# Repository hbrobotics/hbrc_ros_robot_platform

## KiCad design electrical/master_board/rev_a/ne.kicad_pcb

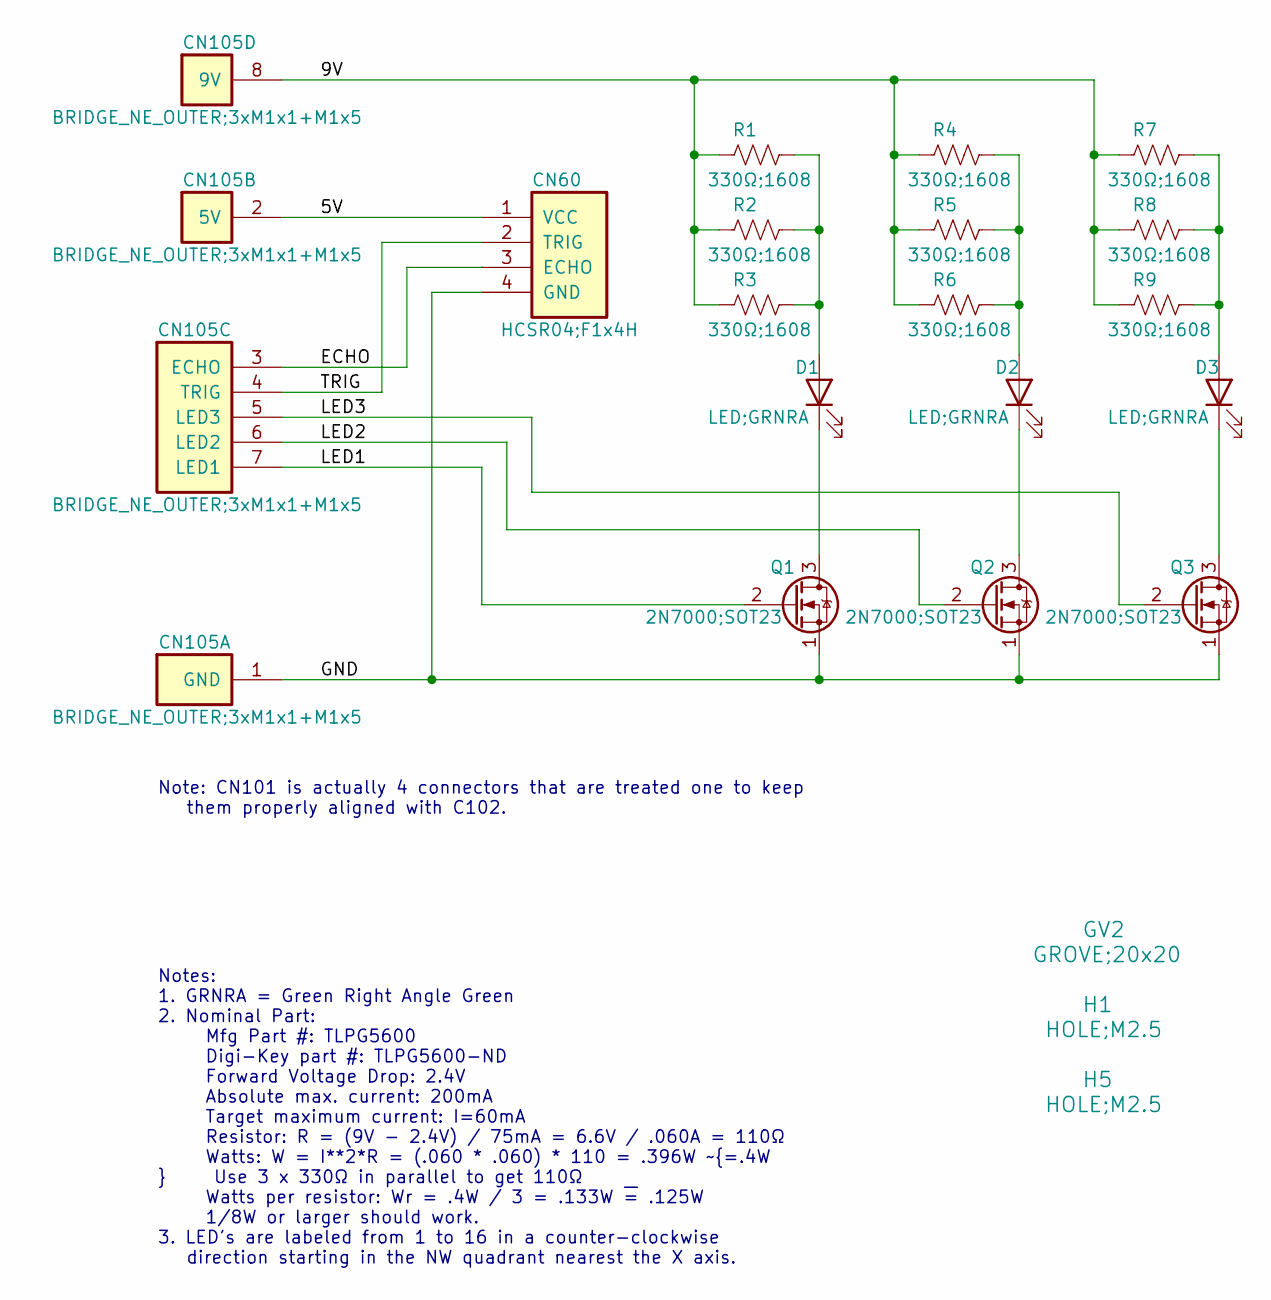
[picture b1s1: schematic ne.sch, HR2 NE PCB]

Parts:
CN60: HCSR04;F1x4H; HCSR04_F1x4H
CN105: BRIDGE_NE_OUTER;3xM1x1+M1x5; BRIDGE_NE_OUTER_3xM1x1+M1x5
D1, D2, D3: LED;GRNRA; LED_GRNRA
GV2: GROVE;20x20; GROVE20x20
H1, H5: HOLE;M2.5; MountingHole_2.7mm_M2.5
Q1, Q2, Q3: 2N7000;SOT23; SOT-23
R1, R2, R3, R4, R5, R6, R7, R8, R9: 330Ω;1608; R_0603_1608Metric

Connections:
/5V: CN60.1 (VCC), CN105.2 (5V)
/9V: CN105.8 (9V), R1.2, R2.2, R3.2, R4.2, R5.2, R6.2, R7.2, R8.2, R9.2
/ECHO: CN60.3 (ECHO), CN105.3 (ECHO)
/GND: CN60.4 (GND), CN105.1 (GND), Q1.1 (S), Q2.1 (S), Q3.1 (S)
/LED1: CN105.7 (LED1), Q1.2 (G)
/LED2: CN105.6 (LED2), Q2.2 (G)
/LED3: CN105.5 (LED3), Q3.2 (G)
/TRIG: CN60.2 (TRIG), CN105.4 (TRIG)
unnamed: D1.1 (K), Q1.3 (D)
unnamed: D1.2 (A), R1.1, R2.1, R3.1
unnamed: D2.1 (K), Q2.3 (D)
unnamed: D2.2 (A), R4.1, R5.1, R6.1
unnamed: D3.1 (K), Q3.3 (D)
unnamed: D3.2 (A), R7.1, R8.1, R9.1

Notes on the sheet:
Notes: 1. GRNRA = Green Right Angle Green 2. Nominal Part: Mfg Part #: TLPG5600 Digi-Key part #: TLPG5600-ND Forward Voltage Drop: 2.4V Absolute max. current: 200mA Target maximum current: I=60mA Resistor: R = (9V - 2.4V) / 75mA = 6.6V / .060A = 110Ω Watts: W = I**2*R = (.060 * .060) * 110 = .396W 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
Note: CN101 is actually 4 connectors that are treated one to keep them properly aligned with C102.

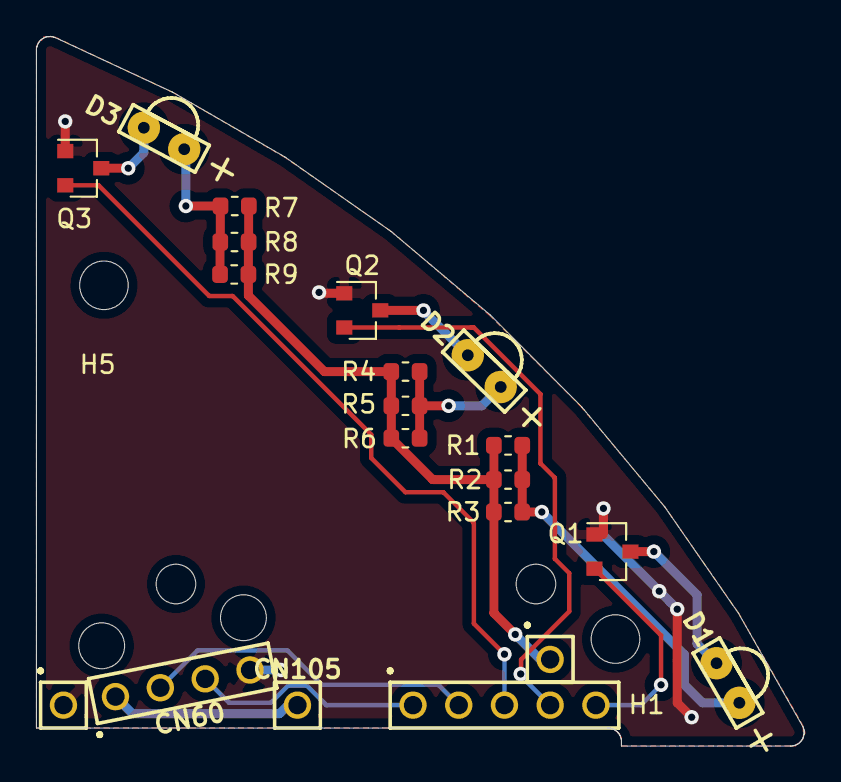
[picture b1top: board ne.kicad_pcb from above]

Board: 2 copper layers, 42.7 x 39.4 mm, 20 parts (1 on the bottom side), 14 nets.

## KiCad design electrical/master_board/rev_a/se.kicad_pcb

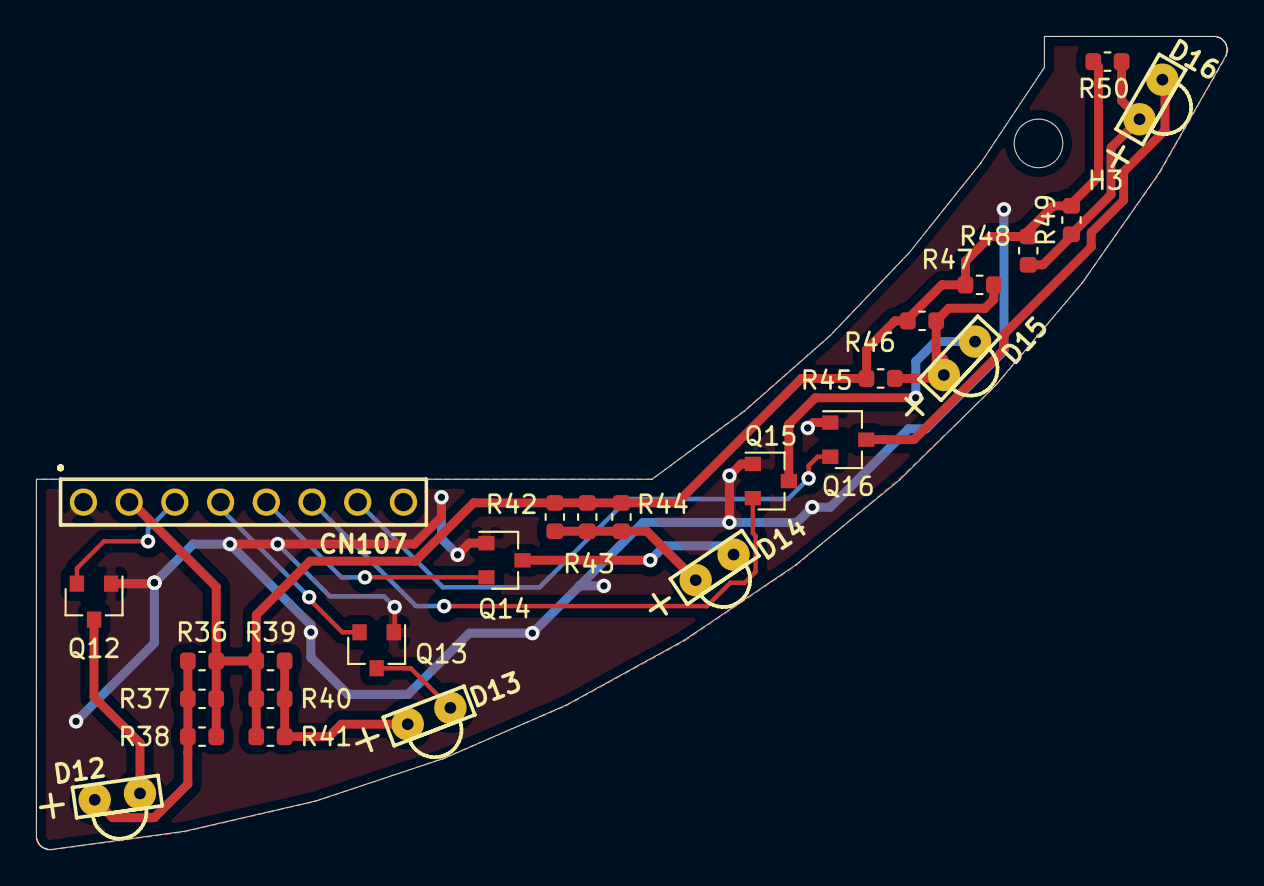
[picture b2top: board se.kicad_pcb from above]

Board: 2 copper layers, 66.2 x 45.2 mm, 27 parts (0 on the bottom side), 17 nets.

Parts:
CN107: BRIDGE_SE_OUTER;M1x8; BRIDGE_SE_OUTER_M1x8
D12, D13, D14, D15, D16: LED;GRNRA; LED_GRNRA
H3: HOLE;M2.5; MountingHole_2.7mm_M2.5
Q12, Q13, Q14, Q15, Q16: 2N7000;SOT23; SOT-23
R36, R37, R38, R39, R40, R41, R42, R43, R44, R45, R46, R47, R48, R49, R50: 330Ω;1608; R_0603_1608Metric

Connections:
/9V: CN107.2, R36.2, R37.2, R38.2, R39.2, R40.2, R41.2, R42.2, R43.2, R44.2, R45.2, R46.2, R47.2, R48.2, R49.2, R50.2
/GND: CN107.1, Q12.1, Q13.1, Q14.1, Q15.1, Q16.1
/LED12: CN107.3, Q12.2
/LED13: CN107.4, Q13.2
/LED14: CN107.5, Q14.2
/LED15: CN107.6, Q15.2
/LED16: CN107.7, Q16.2
unnamed: D12.1, Q12.3
unnamed: D12.2, R36.1, R37.1, R38.1
unnamed: D13.1, Q13.3
unnamed: D13.2, R39.1, R40.1, R41.1
unnamed: D14.1, Q14.3
unnamed: D14.2, R42.1, R43.1, R44.1
unnamed: D15.1, Q15.3
unnamed: D15.2, R45.1, R46.1, R47.1
unnamed: D16.1, Q16.3
unnamed: D16.2, R48.1, R49.1, R50.1

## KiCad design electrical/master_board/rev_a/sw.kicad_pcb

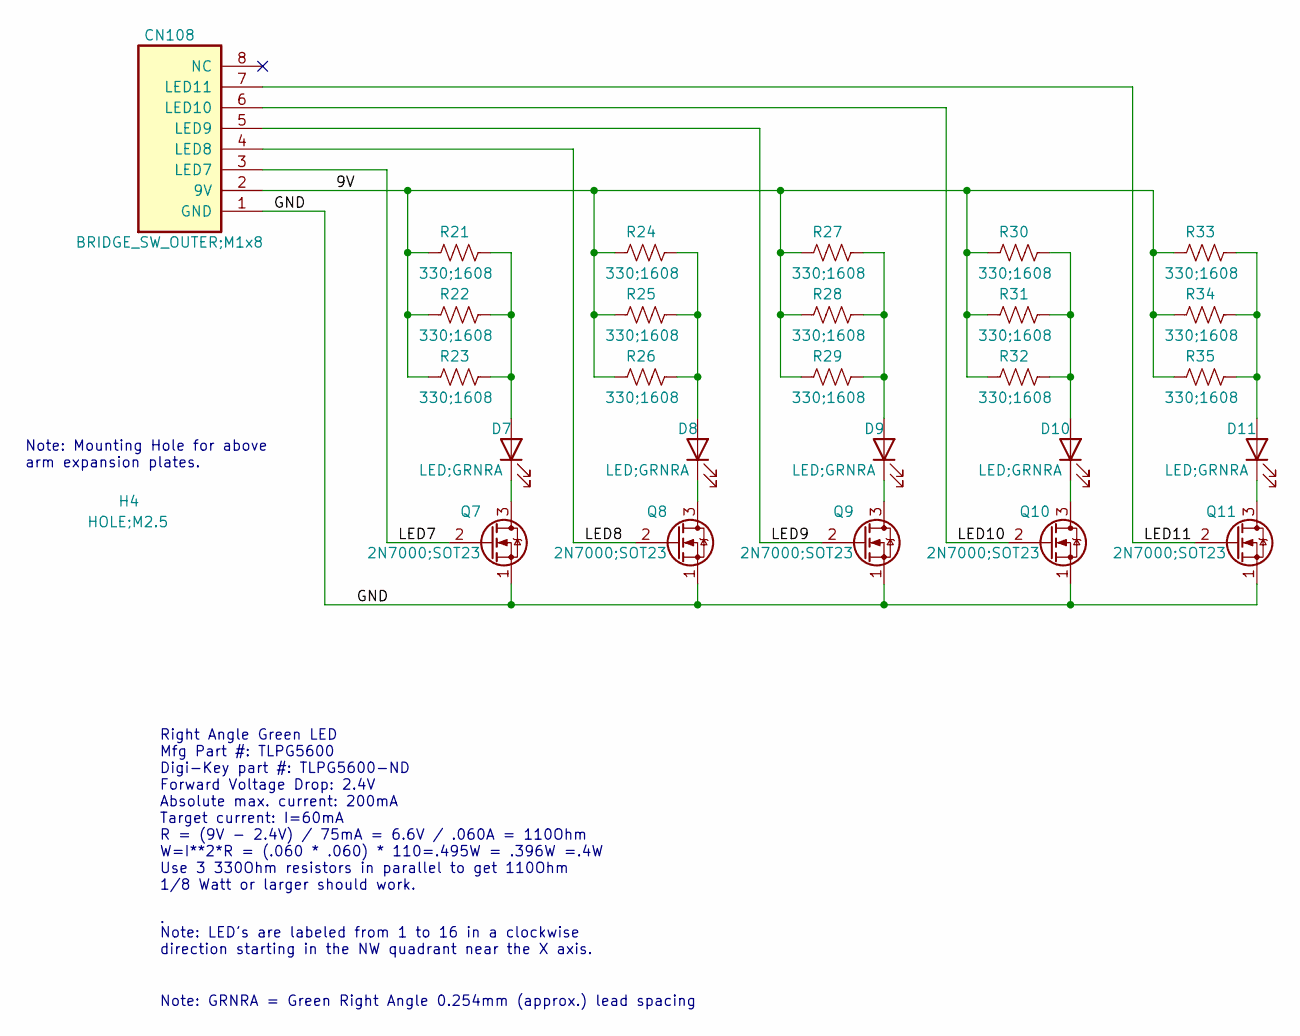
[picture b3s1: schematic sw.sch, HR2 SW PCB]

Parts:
CN108: BRIDGE_SW_OUTER;M1x8; BRIDGE_SW_OUTER_M1x8
D7, D8, D9, D10, D11: LED;GRNRA; LED_GRNRA
H4: HOLE;M2.5; MountingHole_2.7mm_M2.5
Q7, Q8, Q9, Q10, Q11: 2N7000;SOT23; SOT-23
R21, R22, R23, R24, R25, R26, R27, R28, R29, R30, R31, R32, R33, R34, R35: 330;1608; R_0603_1608Metric

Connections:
/9V: CN108.2 (9V), R21.2, R22.2, R23.2, R24.2, R25.2, R26.2, R27.2, R28.2, R29.2, R30.2, R31.2, R32.2, R33.2, R34.2, R35.2
/GND: CN108.1 (GND), Q7.1 (S), Q8.1 (S), Q9.1 (S), Q10.1 (S), Q11.1 (S)
/LED7: CN108.3 (LED7), Q7.2 (G)
/LED8: CN108.4 (LED8), Q8.2 (G)
/LED9: CN108.5 (LED9), Q9.2 (G)
/LED10: CN108.6 (LED10), Q10.2 (G)
/LED11: CN108.7 (LED11), Q11.2 (G)
unnamed: D7.1 (K), Q7.3 (D)
unnamed: D7.2 (A), R21.1, R22.1, R23.1
unnamed: D8.1 (K), Q8.3 (D)
unnamed: D8.2 (A), R24.1, R25.1, R26.1
unnamed: D9.1 (K), Q9.3 (D)
unnamed: D9.2 (A), R27.1, R28.1, R29.1
unnamed: D10.1 (K), Q10.3 (D)
unnamed: D10.2 (A), R30.1, R31.1, R32.1
unnamed: D11.1 (K), Q11.3 (D)
unnamed: D11.2 (A), R33.1, R34.1, R35.1

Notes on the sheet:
Right Angle Green LED Mfg Part #: TLPG5600 Digi-Key part #: TLPG5600-ND Forward Voltage Drop: 2.4V Absolute max. current: 200mA Target current: I=60mA R = (9V - 2.4V) / 75mA = 6.6V / .060A = 110Ohm W=I**2*R = (.060 * .060) * 110=.495W = .396W =.4W Use 3 330Ohm resistors in parallel to get 110Ohm 1/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
Note: GRNRA = Green Right Angle 0.254mm (approx.) lead spacing
Note: LED's are labeled from 1 to 16 in a clockwise direction starting in the NW quadrant near the X axis.
Note: Mounting Hole for above arm expansion plates.

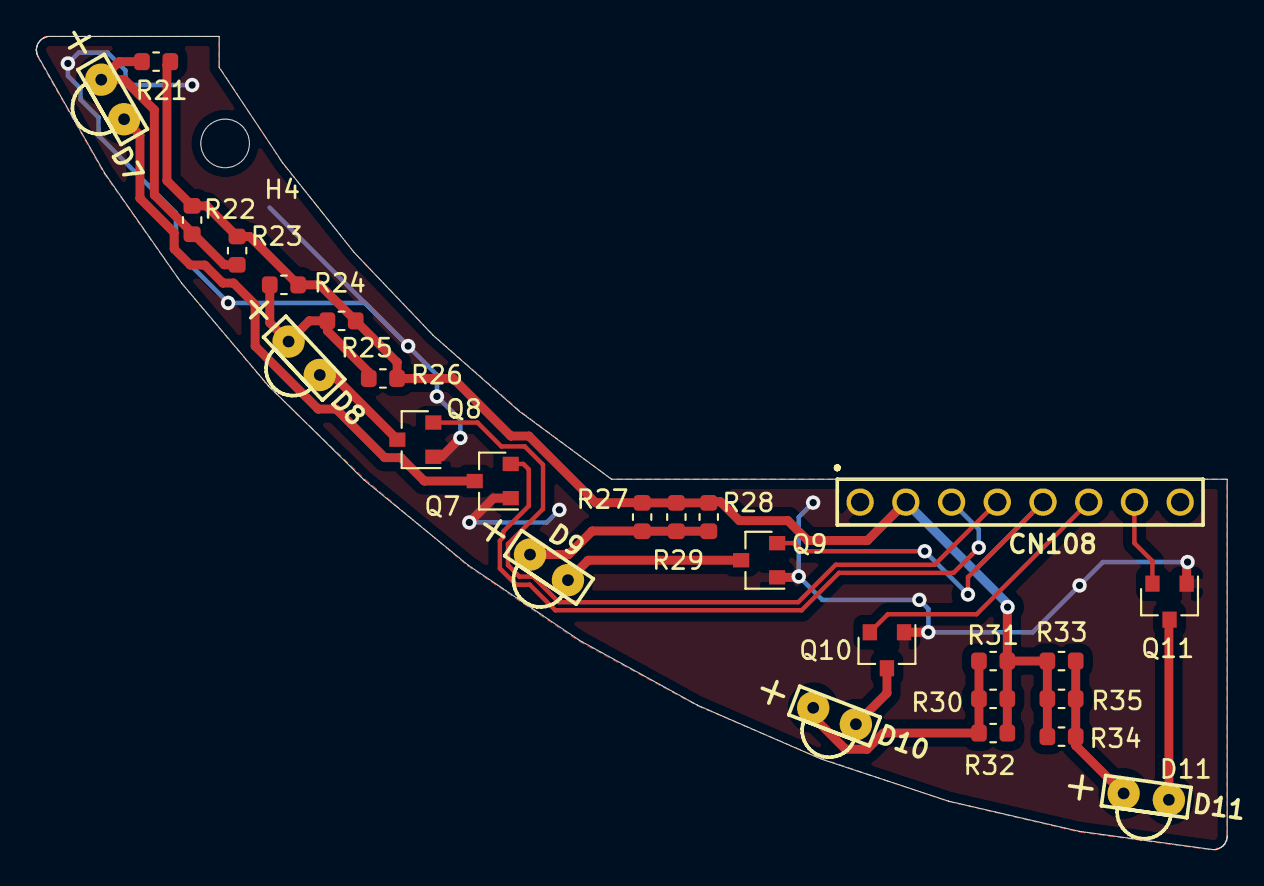
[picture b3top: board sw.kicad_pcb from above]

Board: 2 copper layers, 66.2 x 45.2 mm, 27 parts (0 on the bottom side), 17 nets.
